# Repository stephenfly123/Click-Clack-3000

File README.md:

# Click-Clack-3000 ⌨️

A 4-key custom macropad built with the Seeed Studio XIAO RP2040.

## 🚀 Features
* 4 Mechanical Switches (Cherry MX style)
* Compact PCB design
* Custom 3D printed case
* Powered by KMK (CircuitPython)

## 📂 Folder Structure
* **/PCB**: Contains KiCad schematic and PCB layout files.
* **/Firmware**: Contains the `main.py` code and KMK library.
* **/CAD**: 3D model files (.STL/.STEP) for the enclosure.

## 🛠️ Build Process
1. Designed the PCB in KiCad using the Seeed Xiao footprint.
2. Wrote a custom firmware bot to test typing inputs.
3. Designed/Selected a case for the 4-key layout.

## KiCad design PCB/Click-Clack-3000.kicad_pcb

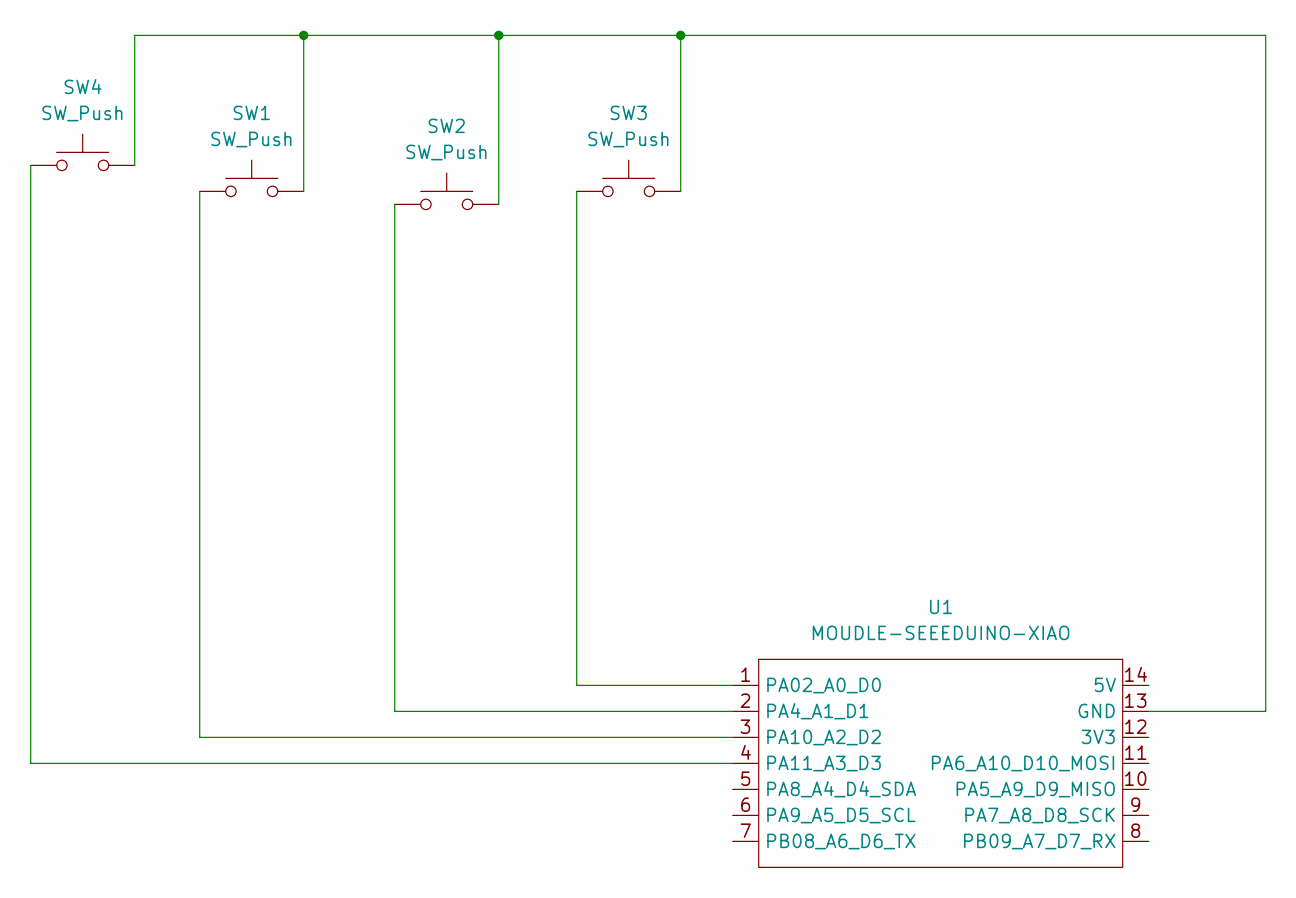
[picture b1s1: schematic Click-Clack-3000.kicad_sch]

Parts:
SW1, SW2, SW3, SW4: SW_Push; SW_Cherry_MX_1.00u_PCB
U1: MOUDLE-SEEEDUINO-XIAO; CERDIP-14_W7.62mm_SideBrazed

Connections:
unnamed: SW1.2, SW2.2, SW3.2, SW4.2, U1.13 (GND)
unnamed: SW3.1, U1.1 (PA02_A0_D0)
unnamed: SW2.1, U1.2 (PA4_A1_D1)
unnamed: SW1.1, U1.3 (PA10_A2_D2)
unnamed: SW4.1, U1.4 (PA11_A3_D3)

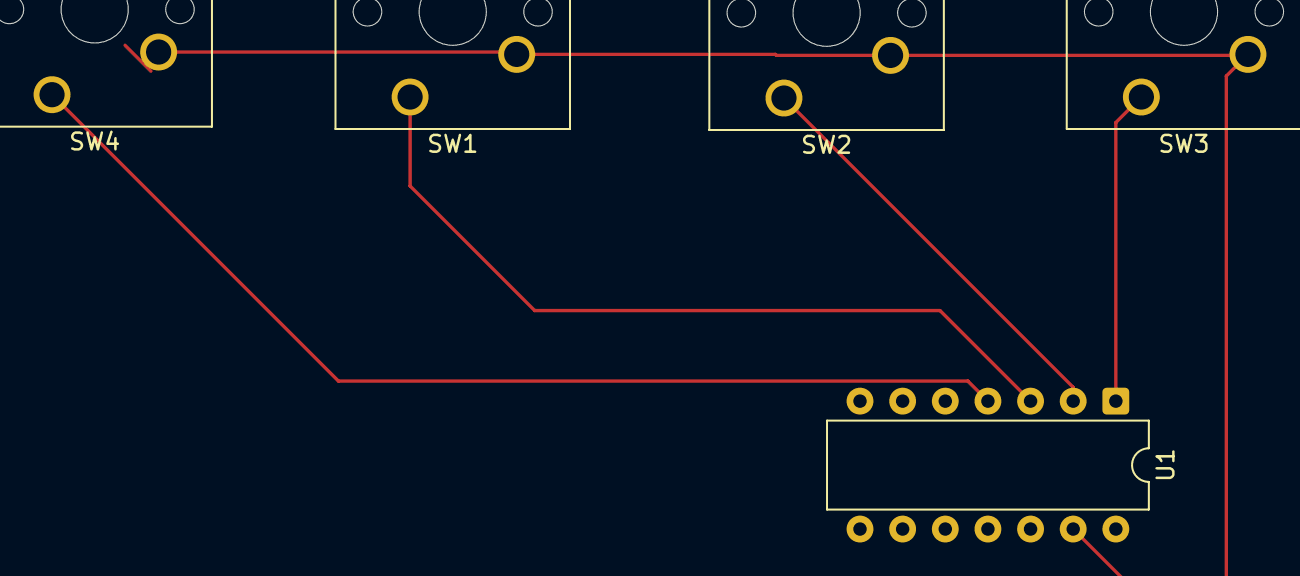
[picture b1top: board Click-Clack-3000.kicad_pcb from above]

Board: 2 copper layers, 5 parts (0 on the bottom side), 5 nets.

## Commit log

2026-02-20 Update README with Click-Clack-3000 description
    Added project description for Click-Clack-3000.
2026-02-23 Revise README.md with detailed project information
    Expanded project description and added features, folder structure, and build process sections.
